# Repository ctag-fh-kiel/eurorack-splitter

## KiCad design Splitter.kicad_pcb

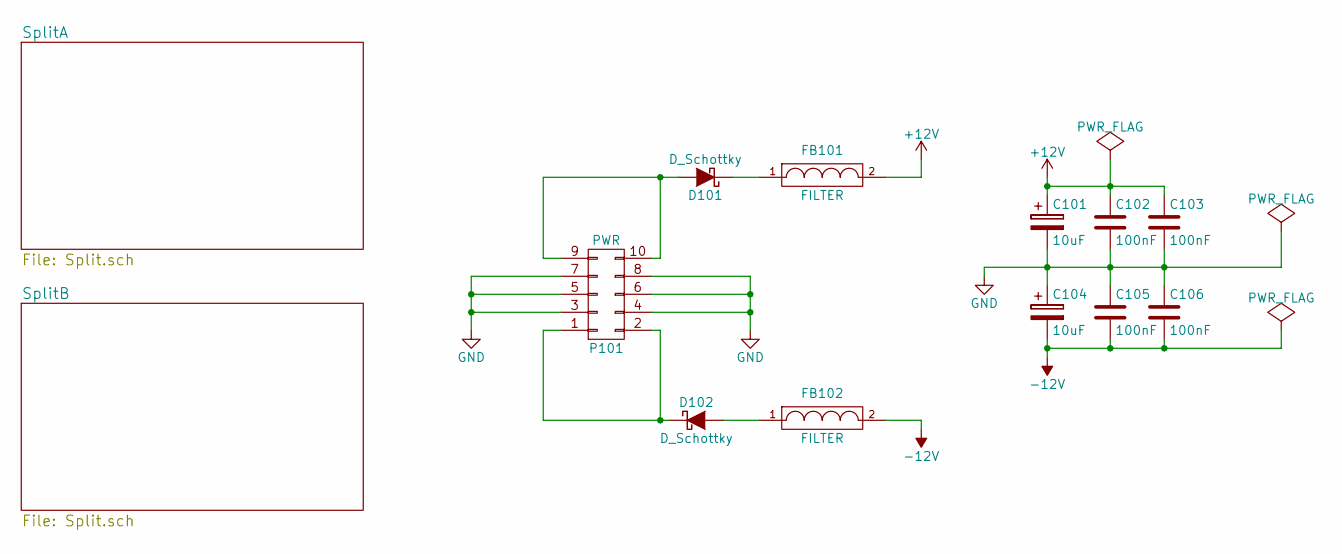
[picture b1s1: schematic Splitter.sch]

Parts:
C101, C104: 10uF; c_elec_4x5.7
C102, C103, C105, C106: 100nF; C_0603_HandSoldering
D101, D102: D_Schottky; Diode-SMA_Standard
FB101, FB102: FILTER; R_0805_HandSoldering
P101: PWR; Pin_Header_Straight_2x05

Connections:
+12V: C101.1, C102.1, C103.1, FB101.2; also elsewhere on the board
-12V: C104.2, C105.2, C106.2, FB102.2; also elsewhere on the board
GND: C101.2, C102.2, C103.2, C104.1, C105.1, C106.1, P101.3, P101.4, P101.5, P101.6, P101.7, P101.8; also elsewhere on the board
unnamed: D101.1 (K), FB101.1
unnamed: D101.2 (A), P101.9, P101.10
unnamed: D102.1 (K), P101.1, P101.2
unnamed: D102.2 (A), FB102.1

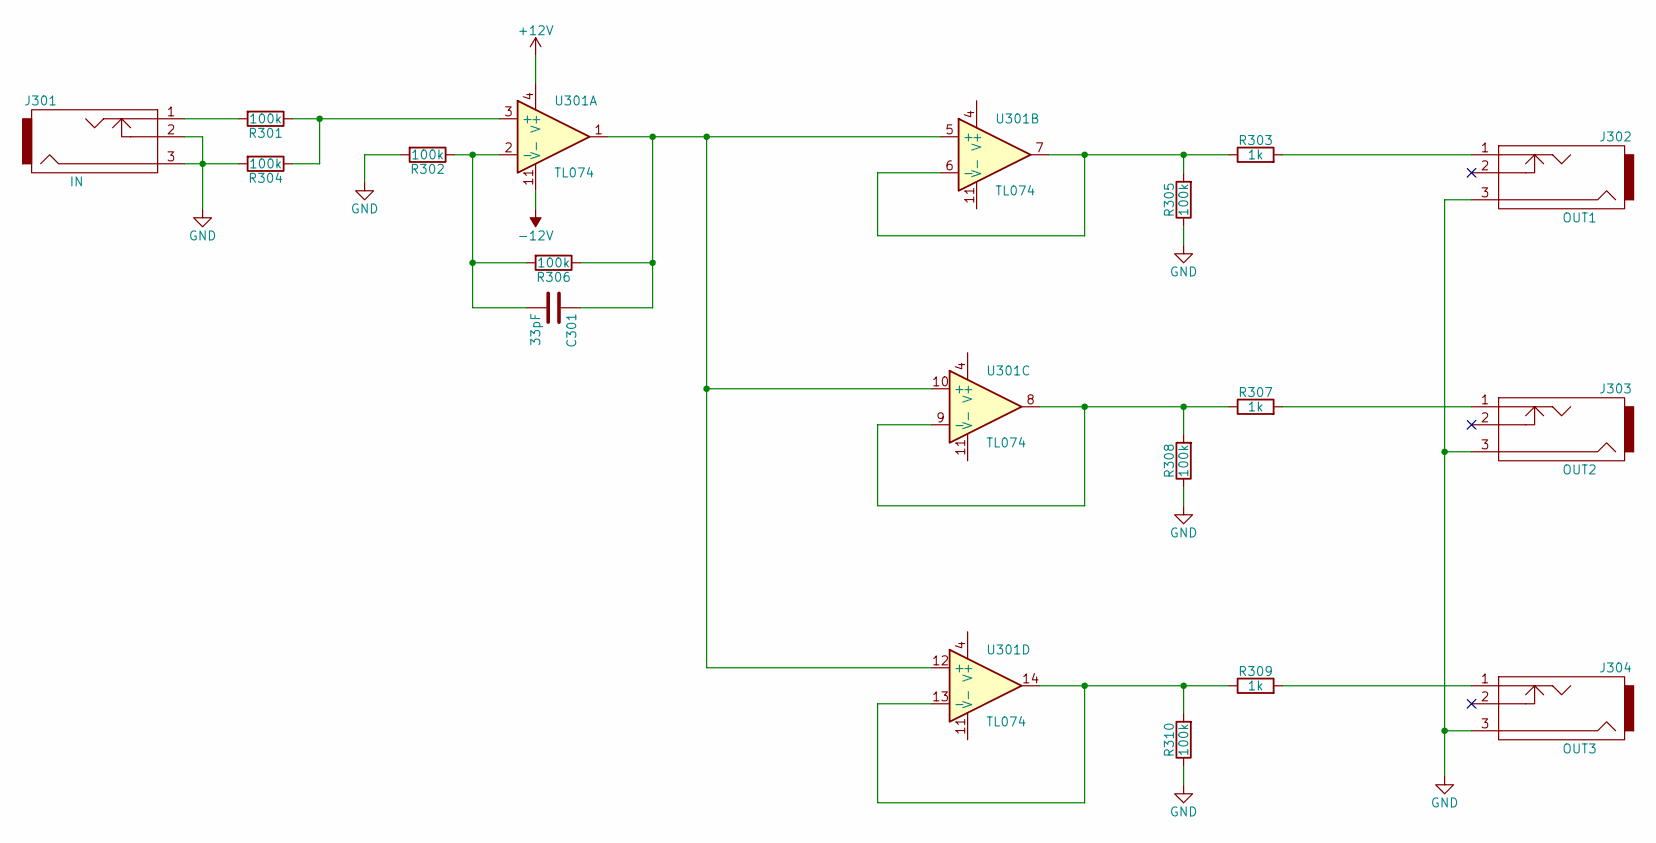
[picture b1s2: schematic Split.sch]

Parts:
C201: 33pF; C_0603_HandSoldering
J201: IN; THONKICONN
J202: OUT1; THONKICONN
J203: OUT2; THONKICONN
J204: OUT3; THONKICONN
R201, R202, R204, R205, R206, R208, R210: 100k; R_0603_HandSoldering
R203, R207, R209: 1k; R_0603_HandSoldering
U201: TL074; TSSOP-14_4.4x5mm_Pitch0.65mm

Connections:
+12V: U201.4 (V+); also elsewhere on the board
-12V: U201.11 (V-); also elsewhere on the board
GND: J201.2, J201.3, J202.3, J203.3, J204.3, R202.2, R204.2, R205.1, R208.1, R210.1; also elsewhere on the board
unnamed: C201.1, R206.1, U201.1, U201.5 (+), U201.10 (+), U201.12 (+)
unnamed: C201.2, R202.1, R206.2, U201.2 (-)
unnamed: J201.1, R201.2
unnamed: J202.1, R203.2
unnamed: J203.1, R207.2
unnamed: J204.1, R209.2
unnamed: R201.1, R204.1, U201.3 (+)
unnamed: R203.1, R205.2, U201.6 (-), U201.7
unnamed: R207.1, R208.2, U201.8, U201.9 (-)
unnamed: R209.1, R210.2, U201.13 (-), U201.14

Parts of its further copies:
C301: 33pF; C_0603_HandSoldering
J301: IN; THONKICONN
J302: OUT1; THONKICONN
J303: OUT2; THONKICONN
J304: OUT3; THONKICONN
R301, R302, R304, R305, R306, R308, R310: 100k; R_0603_HandSoldering
R303, R307, R309: 1k; R_0603_HandSoldering
U301: TL074; TSSOP-14_4.4x5mm_Pitch0.65mm

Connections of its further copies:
+12V: U301.4 (V+); also elsewhere on the board
-12V: U301.11 (V-); also elsewhere on the board
GND: J301.2, J301.3, J302.3, J303.3, J304.3, R302.2, R304.2, R305.1, R308.1, R310.1; also elsewhere on the board
unnamed: C301.1, R306.1, U301.1, U301.5 (+), U301.10 (+), U301.12 (+)
unnamed: C301.2, R302.1, R306.2, U301.2 (-)
unnamed: J301.1, R301.2
unnamed: J302.1, R303.2
unnamed: J303.1, R307.2
unnamed: J304.1, R309.2
unnamed: R301.1, R304.1, U301.3 (+)
unnamed: R303.1, R305.2, U301.6 (-), U301.7
unnamed: R307.1, R308.2, U301.8, U301.9 (-)
unnamed: R309.1, R310.2, U301.13 (-), U301.14

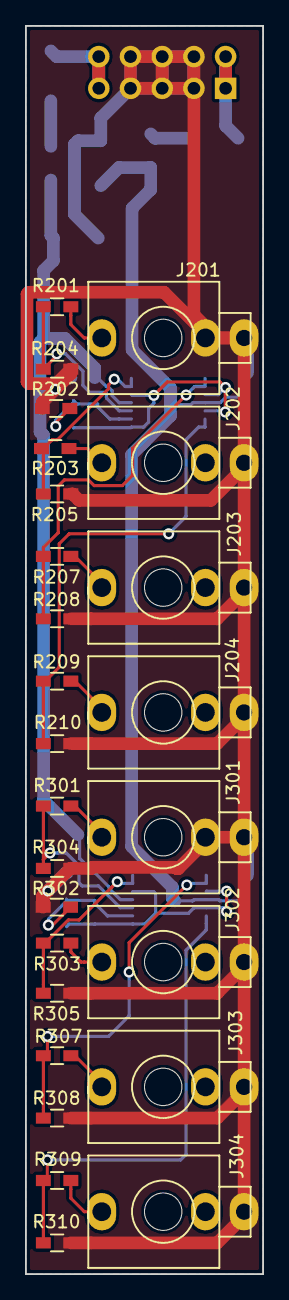
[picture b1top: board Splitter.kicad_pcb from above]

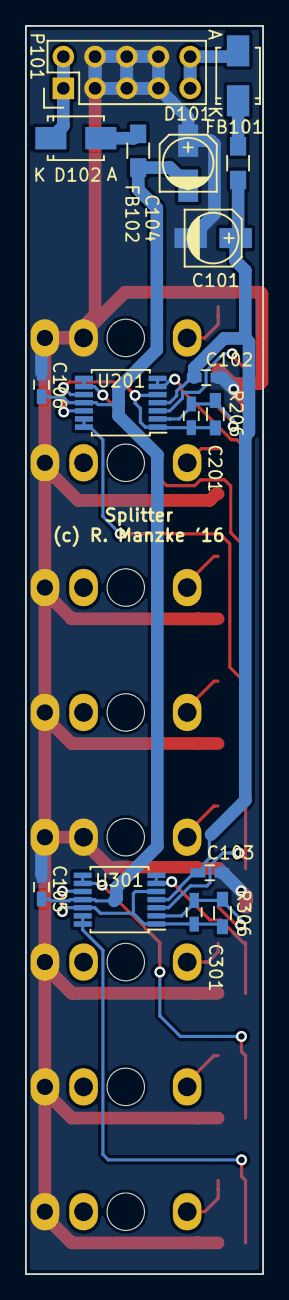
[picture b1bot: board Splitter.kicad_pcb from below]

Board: 2 copper layers, 19.0 x 100.0 mm, 43 parts (17 on the bottom side), 27 nets.

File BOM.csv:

"Id";"Designator";"Package";"Quantity";"Designation";"Supplier and ref";
1;"C101,C104";"c_elec_4x5.7";2;"10uF";;;
2;"C102,C103,C105,C106";"C_0603_HandSoldering";4;"100nF";;;
3;"C201,C301";"C_0603_HandSoldering";2;"33pF";;;
4;"D101,D102";"Diode-SMA_Standard";2;"D_Schottky";;;
5;"FB101,FB102";"R_0805_HandSoldering";2;"FILTER";;;
6;"J201,J301";"THONKICONN";2;"IN";;;
7;"J202,J302";"THONKICONN";2;"OUT1";;;
8;"J203,J303";"THONKICONN";2;"OUT2";;;
9;"J204,J304";"THONKICONN";2;"OUT3";;;
10;"P101";"Pin_Header_Straight_2x05";1;"PWR";;;
11;"R201,R202,R204,R205,R206,R208,R210,R301,R302,R304,R305,R306,R308,R310";"R_0603_HandSoldering";14;"100k";;;
12;"R203,R207,R209,R303,R307,R309";"R_0603_HandSoldering";6;"1k";;;
13;"U201,U301";"TSSOP-14_4.4x5mm_Pitch0.65mm";2;"TL074";;;

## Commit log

2021-08-02 init
